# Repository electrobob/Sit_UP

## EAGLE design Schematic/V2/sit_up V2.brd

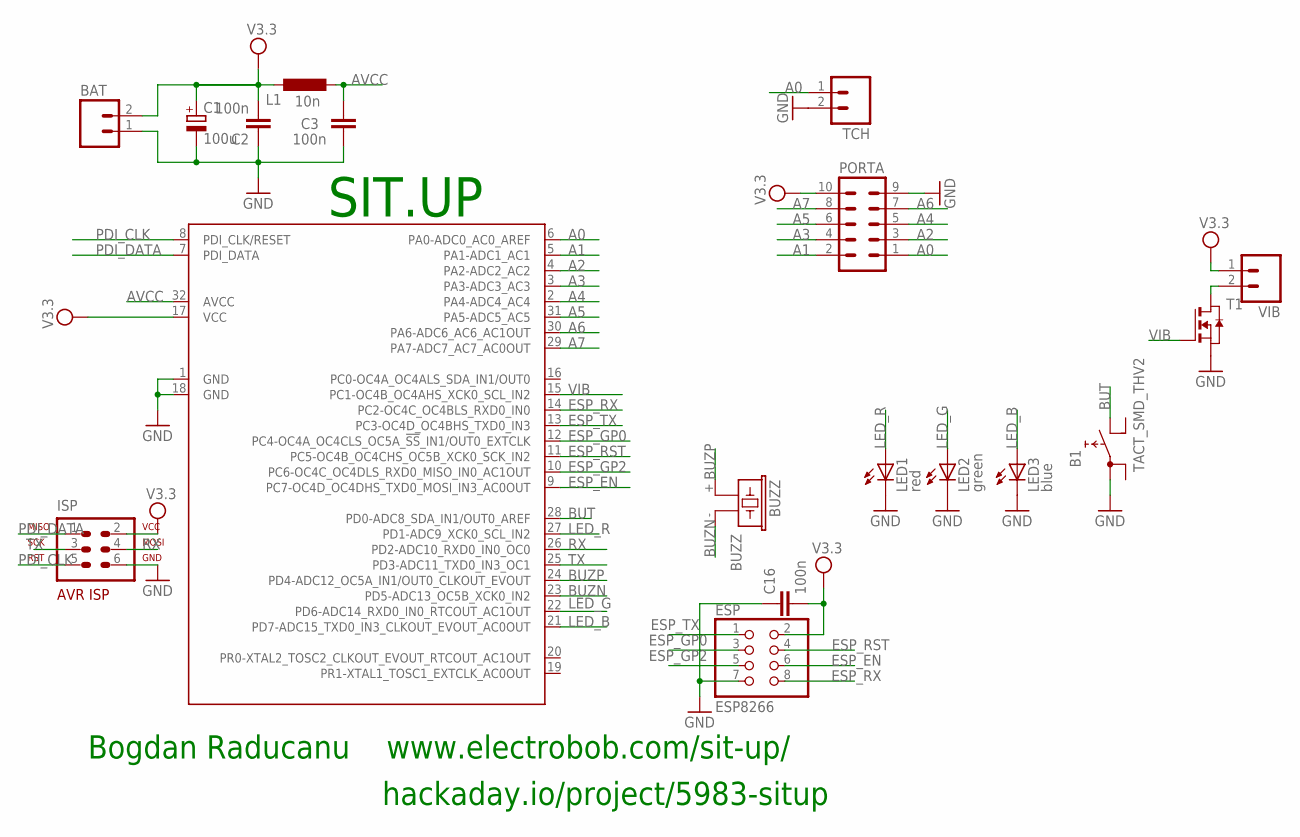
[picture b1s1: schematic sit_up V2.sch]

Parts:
B1: TACT_SMD_THV2; TACT_6MM_SMD_2
BAT: M02; 02P
BUZZ: BUZZ; F/CM12P
C1: 100u; 153CLV-0505
C2, C3, C16: 100n; C0805
ESP: ESP8266; 2X04
ISP: AVR-ISP-6VERT; AVR-ISP-6
L1: 10n; L2012C
LED1: red; LED3MM
LED2: green; LED3MM
LED3: blue; LED3MM
PORTA: MA05-2_PORT; MA05_PORT
T1: NMOSSOT23; SOT-23
TCH: M02; 02P
VIB: M02; 02P
XMEGA: XMEGA; TQFP32

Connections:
A0: PORTA.1, TCH.1, XMEGA.6 (PA0-ADC0_AC0_AREF)
A1: PORTA.2, XMEGA.5 (PA1-ADC1_AC1)
A2: PORTA.3, XMEGA.4 (PA2-ADC2_AC2)
A3: PORTA.4, XMEGA.3 (PA3-ADC3_AC3)
A4: PORTA.5, XMEGA.2 (PA4-ADC4_AC4)
A5: PORTA.6, XMEGA.31 (PA5-ADC5_AC5)
A6: PORTA.7, XMEGA.30 (PA6-ADC6_AC6_AC1OUT)
A7: PORTA.8, XMEGA.29 (PA7-ADC7_AC7_AC0OUT)
AVCC: C3.2, L1.2, XMEGA.32 (AVCC)
BUT: B1.P$2 (2A), XMEGA.28 (PD0-ADC8_SDA_IN1/OUT0_AREF)
BUZN: BUZZ.- (2), XMEGA.23 (PD5-ADC13_OC5B_XCK0_IN2)
BUZP: BUZZ.+ (1), XMEGA.24 (PD4-ADC12_OC5A_IN1/OUT0_CLKOUT_EVOUT)
ESP_EN: ESP.6, XMEGA.9 (PC7-OC4D_OC4DHS_TXD0_MOSI_IN3_AC0OUT)
ESP_GP0: ESP.3, XMEGA.12 (PC4-OC4A_OC4CLS_OC5A_!SS!_IN1/OUT0_EXTC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)
ESP_GP2: ESP.5, XMEGA.10 (PC6-OC4C_OC4DLS_RXD0_MISO_IN0_AC1OUT)
ESP_RST: ESP.4, XMEGA.11 (PC5-OC4B_OC4CHS_OC5B_XCK0_SCK_IN2)
ESP_RX: ESP.8, XMEGA.14 (PC2-OC4C_OC4BLS_RXD0_IN0)
ESP_TX: ESP.1, XMEGA.13 (PC3-OC4D_OC4BHS_TXD0_IN3)
GND: B1.P$1 (1A), BAT.1, C1.-, C2.1, C3.1, C16.1, ESP.7, ISP.6, LED1.K (C), LED2.K (C), LED3.K (C), PORTA.9, T1.2 (S), TCH.2, XMEGA.1 (GND), XMEGA.18 (GND)
LED_B: LED3.A, XMEGA.21 (PD7-ADC15_TXD0_IN3_CLKOUT_EVOUT_AC0OUT)
LED_G: LED2.A, XMEGA.22 (PD6-ADC14_RXD0_IN0_RTCOUT_AC1OUT)
LED_R: LED1.A, XMEGA.27 (PD1-ADC9_XCK0_SCL_IN2)
unnamed: T1.1 (D), VIB.2
PDI_CLK: ISP.5, XMEGA.8 (PDI_CLK/RESET)
PDI_DATA: ISP.1, XMEGA.7 (PDI_DATA)
RX: ISP.4, XMEGA.26 (PD2-ADC10_RXD0_IN0_OC0)
TX: ISP.3, XMEGA.25 (PD3-ADC11_TXD0_IN3_OC1)
V3.3: BAT.2, C1.+, C2.2, C16.2, ESP.2, ISP.2, L1.1, PORTA.10, VIB.1, XMEGA.17 (VCC)
VIB: T1.3 (G), XMEGA.15 (PC1-OC4B_OC4AHS_XCK0_SCL_IN2)

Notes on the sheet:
Bogdan Raducanu www.electrobob.com/sit-up/
SIT.UP
hackaday.io/project/5983-situp

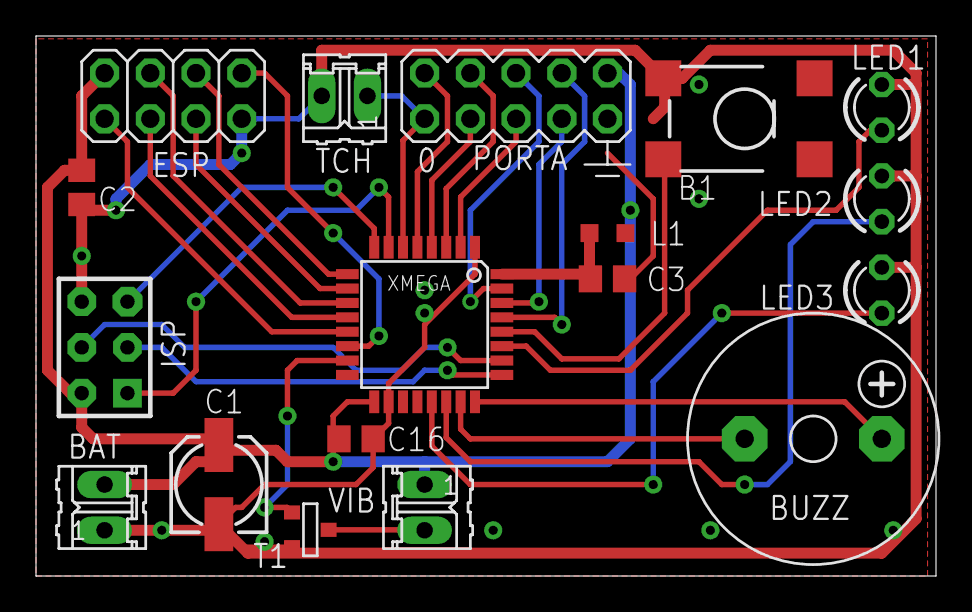
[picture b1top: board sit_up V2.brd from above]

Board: 2 copper layers, 50.0 x 30.0 mm, 18 parts (0 on the bottom side), 29 nets.

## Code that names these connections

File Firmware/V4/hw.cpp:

/*
 * SitUp - AUX Hardware functions
 * Created: 08.06.2015
 *  Author: Bogdan Raducanu
 * copyright (c) Bogdan Raducanu, 2015
 * http://www.electrobob.com/sit-up/
 * bogdan@electrobob.com
 * Released under GPLv3.
 * Please refer to LICENSE file for licensing information.
 */

#include <avr/io.h>
#include <util/delay.h>
#include <asf.h>
#include "hw.h"

void buzz_init() {
	ioport_set_pin_dir(BUZZER_PIN_P, IOPORT_DIR_OUTPUT);
	ioport_set_pin_dir(BUZZER_PIN_N, IOPORT_DIR_OUTPUT);

}

void buzz_a_bit(uint16_t buzz_time_ms) {
	for (uint16_t i = 0; i < buzz_time_ms * 2; i++) {
		ioport_set_pin_level(BUZZER_PIN_N, false);
		ioport_set_pin_level(BUZZER_PIN_P, true);
		_delay_us(250);
		ioport_set_pin_level(BUZZER_PIN_N, true);
		ioport_set_pin_level(BUZZER_PIN_P, false);
		_delay_us(250);
	}
			ioport_set_pin_level(BUZZER_PIN_N, false); //make sure both pins are L at end of buzzing
			ioport_set_pin_level(BUZZER_PIN_P, false);
}

void LED_init(void) {
	ioport_set_pin_dir(LED_R_PIN, IOPORT_DIR_OUTPUT);
	ioport_set_pin_dir(LED_G_PIN, IOPORT_DIR_OUTPUT);
	ioport_set_pin_dir(LED_B_PIN, IOPORT_DIR_OUTPUT);
}

void LED_R_ON(void) {
	ioport_set_pin_level(LED_R_PIN, true);
}
void LED_R_OFF(void) {
	ioport_set_pin_level(LED_R_PIN, false);
}

void LED_G_ON(void) {
	ioport_set_pin_level(LED_G_PIN, true);
}
void LED_G_OFF(void) {
	ioport_set_pin_level(LED_G_PIN, false);
}
void LED_B_ON(void) {
	ioport_set_pin_level(LED_B_PIN, true);
}
void LED_B_OFF(void) {
	ioport_set_pin_level(LED_B_PIN, false);
}

void LED_R_blink(uint16_t dur_ms) {
	LED_R_ON();
	for (uint16_t i = 0; i < dur_ms; i++)
		_delay_ms(1);
	LED_R_OFF();
}

void LED_G_blink(uint16_t dur_ms) {
	LED_G_ON();
	for (uint16_t i = 0; i < dur_ms; i++)
	_delay_ms(1);
	LED_G_OFF();
}

void LED_B_blink(uint16_t dur_ms) {
	LED_B_ON();
	for (uint16_t i = 0; i < dur_ms; i++)
	_delay_ms(1);
	LED_B_OFF();
}



void vib_init(void) {
	//PORTD.DIRSET = 0xB0; //PC7, 5, 4 as outputs
	ioport_set_pin_dir(VIB_PIN, IOPORT_DIR_OUTPUT);
	ioport_set_pin_level(VIB_PIN, false);
}

void vib_on(uint16_t del) {
	ioport_set_pin_level(VIB_PIN, true);
	for (uint16_t i = 0; i < del; i++) {
		_delay_ms(1);
	}
	ioport_set_pin_level(VIB_PIN, false);
}

void vib_off(void) {
	ioport_set_pin_level(VIB_PIN, false);
}

void vib_pulse(uint8_t numbers, uint16_t on_t, uint16_t off_t) {
	for (uint16_t i = 0; i < numbers; i++) {
		vib_on(on_t);
		for (uint16_t j = 0; j < off_t; j++) {
			_delay_ms(1);
		}
	}
}

void vib_15min(void) {
	vib_pulse(4, 150, 250);
}

void vib_1h(void) {
	vib_pulse(10, 250, 500);
}

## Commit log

2015-08-12 :neckbeard: Added .gitattributes
2015-08-12 Sit.Up alerts you when sitting too much
    Initial
2015-09-21 Version 2
    Contains HW V4 and FW V4
